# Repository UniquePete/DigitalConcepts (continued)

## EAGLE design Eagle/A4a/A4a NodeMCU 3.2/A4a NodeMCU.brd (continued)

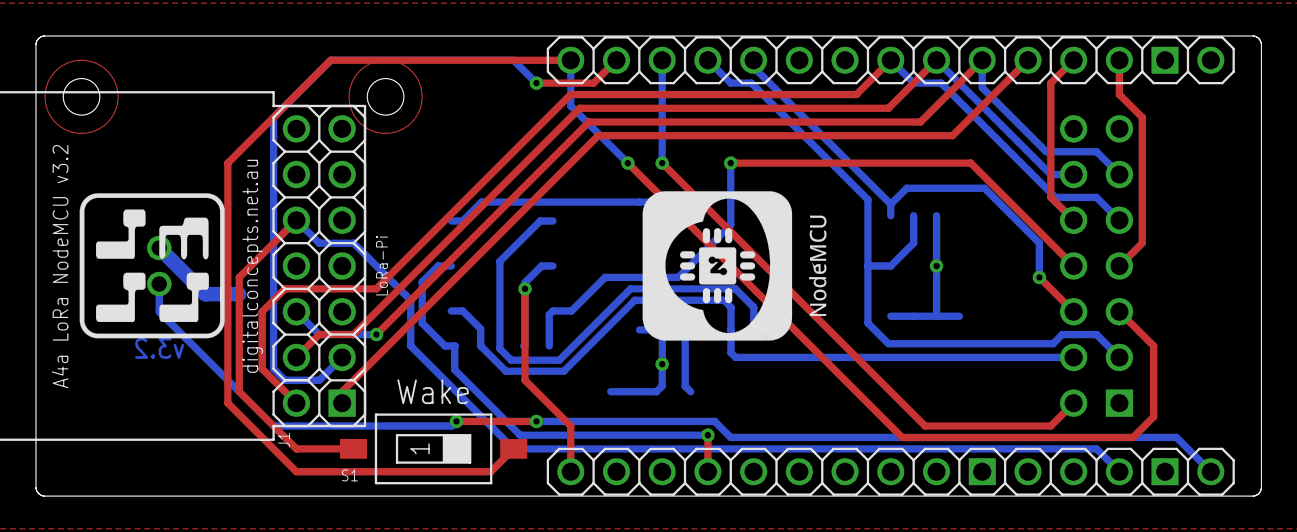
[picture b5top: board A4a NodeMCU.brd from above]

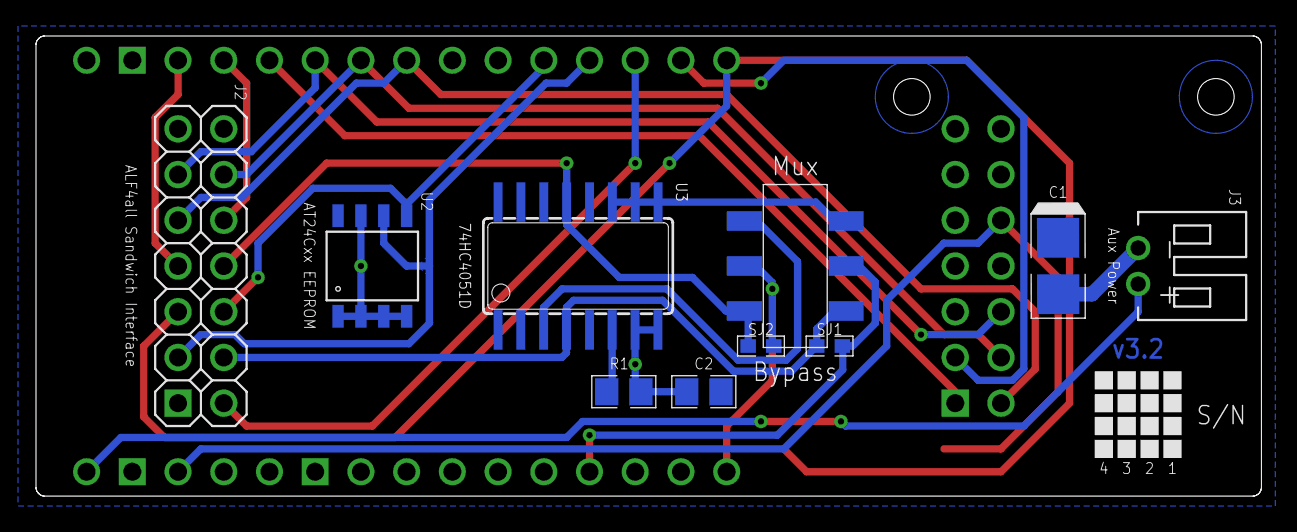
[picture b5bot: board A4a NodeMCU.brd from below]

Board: 2 copper layers, 68.1 x 25.6 mm, 13 parts (9 on the bottom side), 22 nets.

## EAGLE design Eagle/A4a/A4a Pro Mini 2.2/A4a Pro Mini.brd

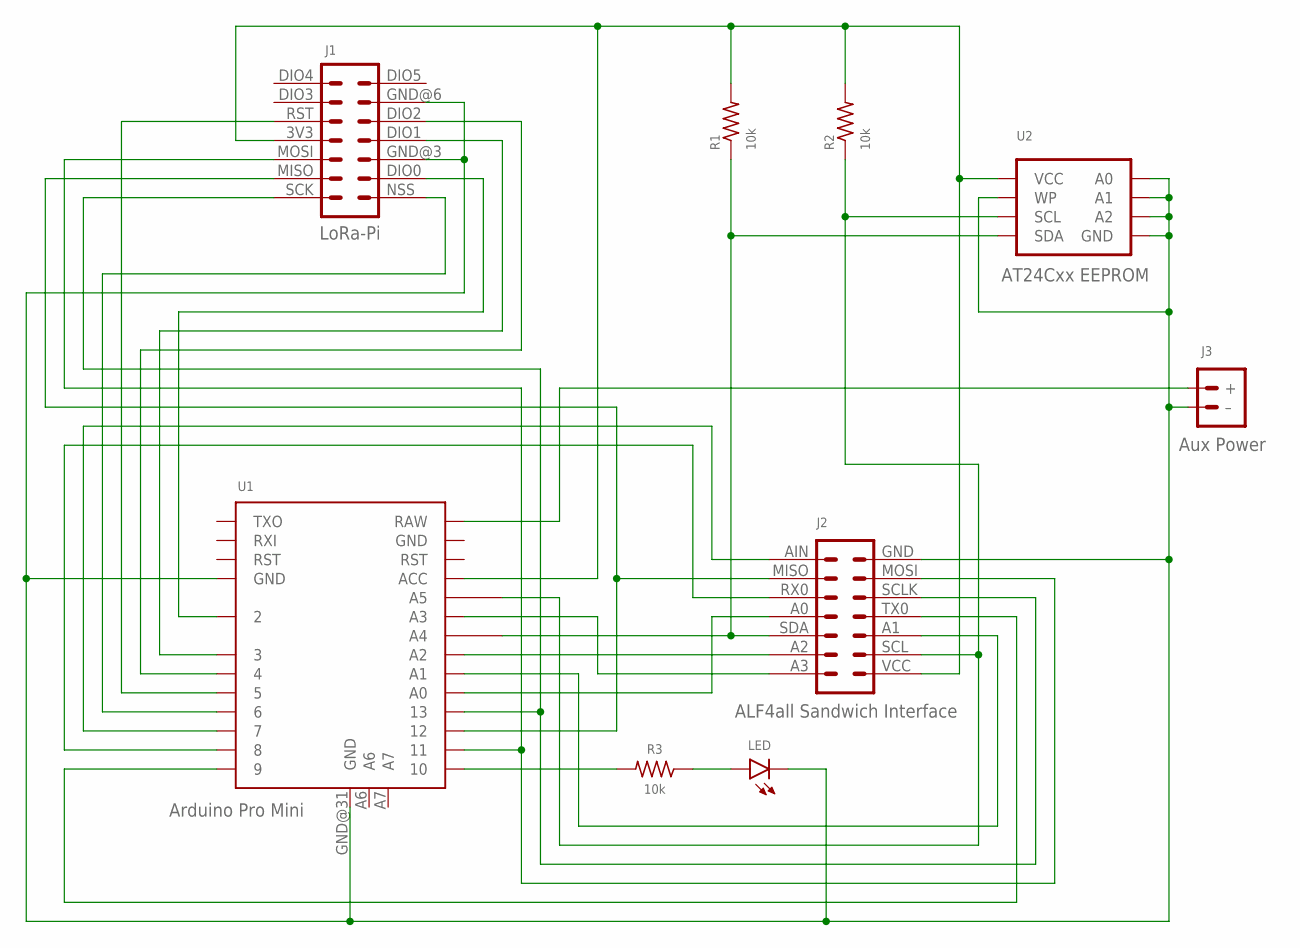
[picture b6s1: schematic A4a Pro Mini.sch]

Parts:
J1: LoRa-Pi; RFM95W-PI
J2: ALF4all Sandwich Interface; CONN_2X7-ALF4ALL-PROCESSOR-B
J3: Aux Power; JST-PH2.0-2-HORIZONTAL
LED: LEDCHIP-LED0805; CHIP-LED0805
R1, R2, R3: 10k; R0805
U1: Arduino Pro Mini; ARDUINO-PRO-MINI-35
U2: AT24Cxx EEPROM; SOP-8

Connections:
GND: J1.GND@3 (3), J1.GND@6 (6), J2.GND (7), J3.- (–), LED.C, U1.GND@22 (GND), U1.GND@31 (GND), U2.P$1 (A0), U2.P$2 (A1), U2.P$3 (A2), U2.P$4 (GND), U2.P$7 (WP)
unnamed: J2.A0 (11), U1.A0
unnamed: J2.A1 (3), U1.A1
unnamed: J2.A2 (13), U1.A2
unnamed: J2.A3 (14), U1.A3
unnamed: J3.+, U1.RAW
unnamed: J1.SCK (14), J2.SCLK (5), U1.13
unnamed: J2.RX0 (10), U1.8
unnamed: J2.AIN (8), U1.7
unnamed: J2.SDA (12), R1.1, U1.A4, U2.P$5 (SDA)
unnamed: J2.SCL (2), R2.1, U1.A5, U2.P$6 (SCL)
unnamed: J1.MISO (13), J2.MISO (9), U1.12
unnamed: J1.MOSI (12), J2.MOSI (6), U1.11
unnamed: J2.TX0 (4), U1.9
unnamed: J1.NSS (1), U1.6
unnamed: J1.RST (10), U1.5
unnamed: J1.DIO2 (5), U1.4
unnamed: J1.DIO1 (4), U1.3
unnamed: J1.DIO0 (2), U1.2
unnamed: R3.2, U1.10
unnamed: LED.A, R3.1
VCC: J1.3V3 (11), J2.VCC (1), R1.2, R2.2, U1.ACC, U2.P$8 (VCC)

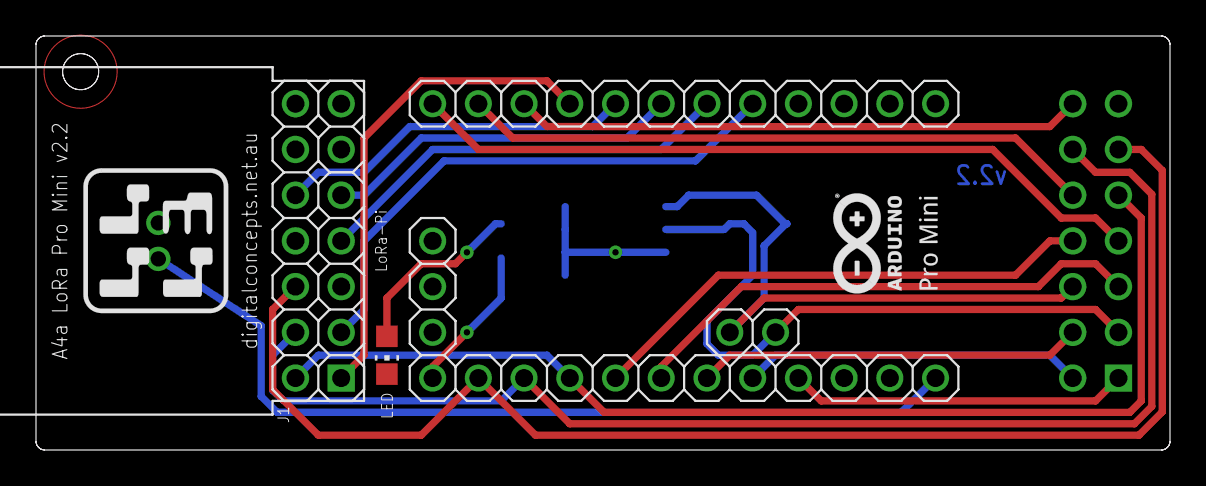
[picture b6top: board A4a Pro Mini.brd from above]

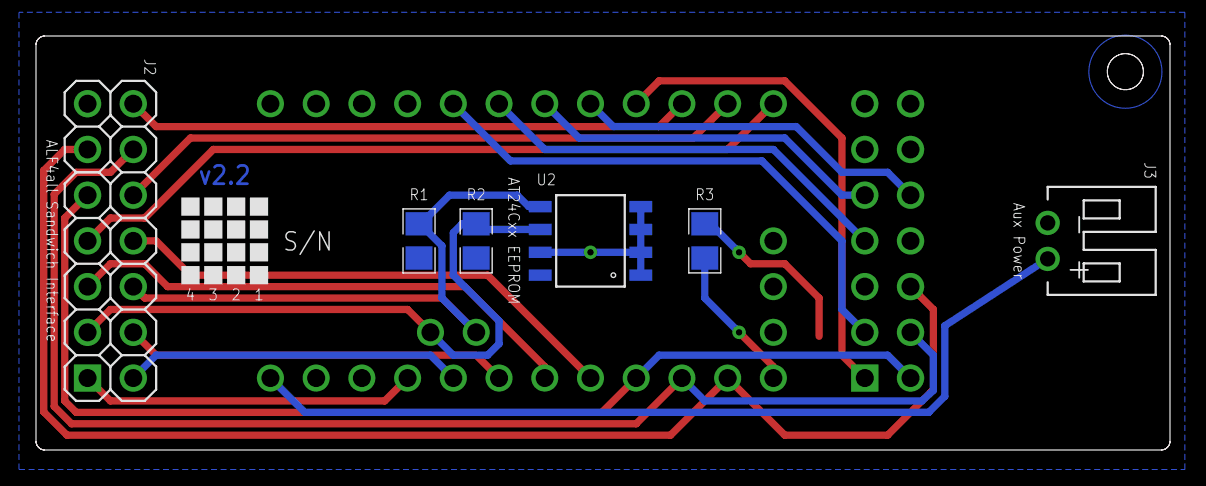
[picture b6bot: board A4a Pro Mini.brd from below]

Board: 2 copper layers, 63.0 x 23.0 mm, 9 parts (5 on the bottom side), 22 nets.
